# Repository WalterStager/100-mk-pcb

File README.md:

# 100-mk-pcb
PCB design for 100% mechanical keyboard

Libraries used in this project  
https://github.com/tmk/kicad_lib_tmk  
https://github.com/tmk/keyboard_parts.pretty  
https://github.com/egladman/keebs.pretty  
https://github.com/ai03-2725/Type-C.pretty

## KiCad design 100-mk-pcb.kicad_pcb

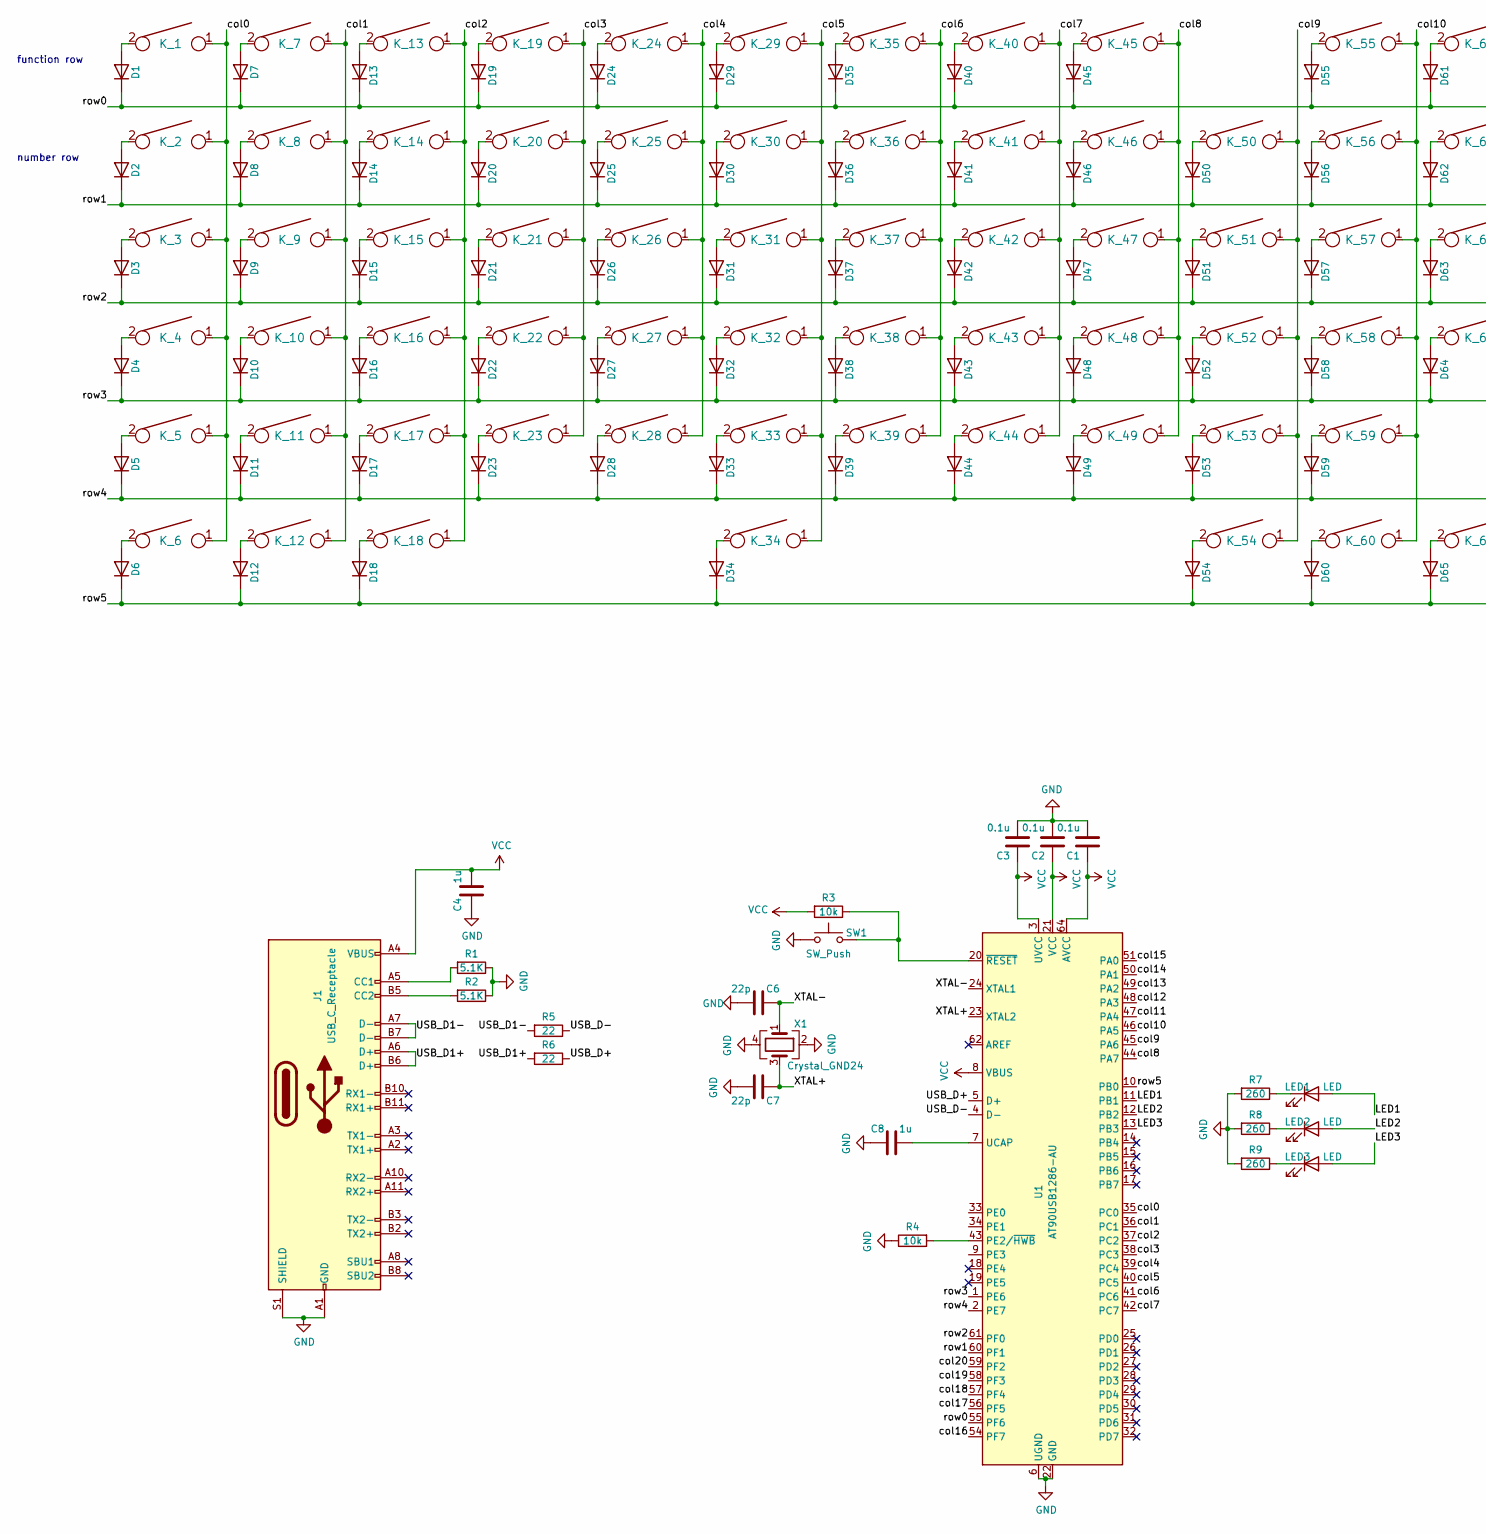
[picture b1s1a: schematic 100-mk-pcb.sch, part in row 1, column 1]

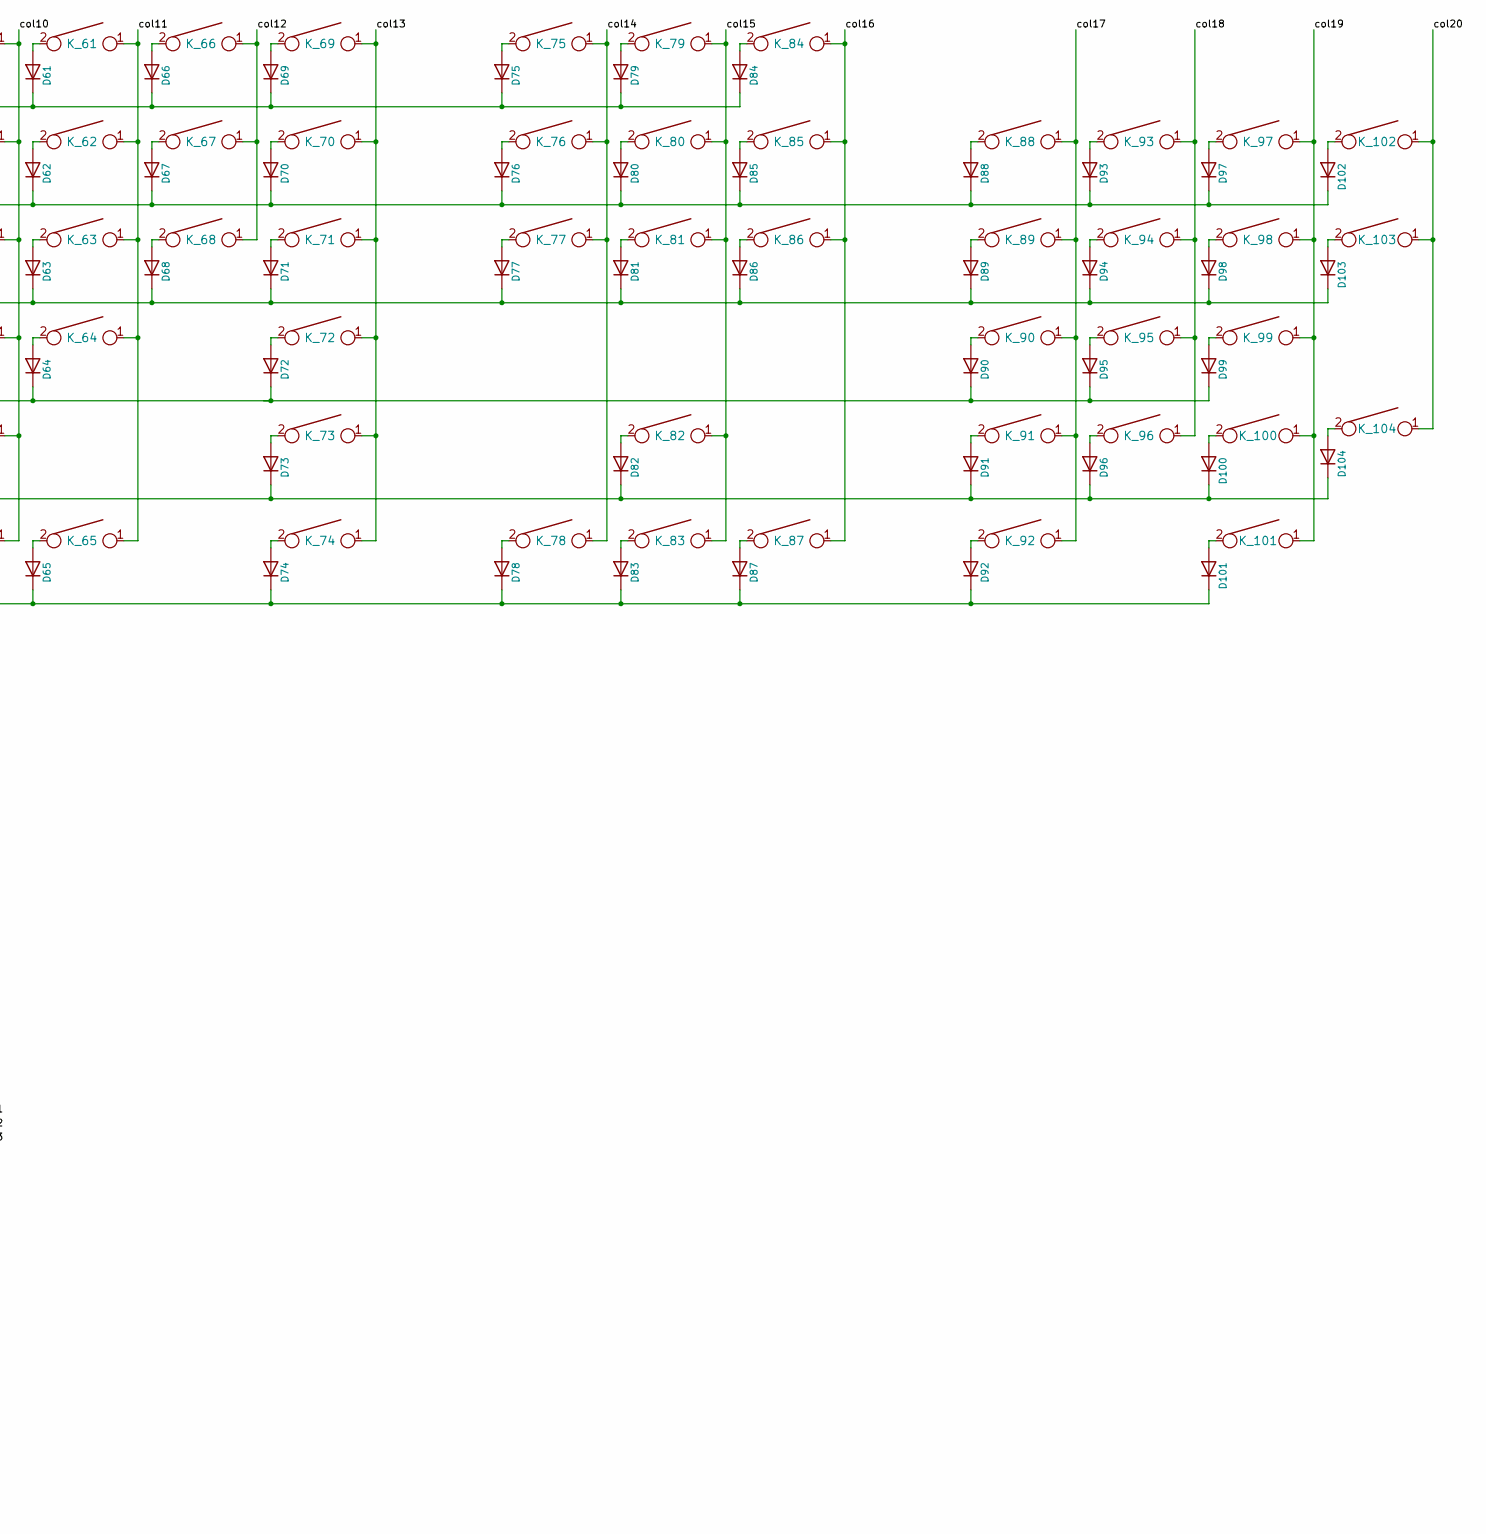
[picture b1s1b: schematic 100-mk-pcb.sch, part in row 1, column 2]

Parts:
C1, C2, C3: 0.1u; C_0805_2012Metric_Pad1.18x1.45mm_HandSolder
C4, C8: 1u; C_0805_2012Metric_Pad1.18x1.45mm_HandSolder
C6, C7: 22p; C_0805_2012Metric_Pad1.18x1.45mm_HandSolder
D1, D2, D3, D4, D5, D6, D7, D8, D9, D10, D11, D12, D13, D14, D15, D16, D17, D18, D19, D20, D21, D22, D23, D24, D25, D26, D27, D28, D29, D30, D31, D32, D33, D34, D35, D36, D37, D38, D39, D40, D41, D42, D43, D44, D45, D46, D47, D48, D49, D50, D51, D52, D53, D54, D55, D56, D57, D58, D59, D60, D61, D62, D63, D64, D65, D66, D67, D68, D69, D70, D71, D72, D73, D74, D75, D76, D77, D78, D79, D80, D81, D82, D83, D84, D85, D86, D87, D88, D89, D90, D91, D92, D93, D94, D95, D96, D97, D98, D99, D100, D101, D102, D103, D104: D; D_SOD123_axial
J1: USB_C_Receptacle; USB_C_GCT_USB4085
K_1, K_2, K_7, K_8, K_9, K_10, K_11, K_12, K_13, K_14, K_15, K_16, K_17, K_19, K_20, K_21, K_22, K_23, K_24, K_25, K_26, K_27, K_28, K_29, K_30, K_31, K_32, K_33, K_35, K_36, K_37, K_38, K_39, K_40, K_41, K_42, K_43, K_44, K_45, K_46, K_47, K_48, K_49, K_50, K_51, K_52, K_53, K_55, K_56, K_57, K_58, K_59, K_60, K_61, K_62, K_63, K_64, K_65, K_66, K_67, K_68, K_69, K_75, K_76, K_77, K_78, K_79, K_80, K_81, K_82, K_83, K_84, K_85, K_86, K_87, K_88, K_89, K_90, K_91, K_93, K_94, K_95, K_96, K_97, K_98, K_99, K_100, K_101, K_102: KEYSW; SW_Cherry_MX_1.00u_PCB
K_3, K_6, K_54, K_71, K_74: KEYSW; SW_Cherry_MX_1.50u_PCB
K_4: KEYSW; SW_Cherry_MX_1.75u_PCB
K_5, K_72: KEYSW; SW_Cherry_MX_2.25u_PCB
K_18: KEYSW; SW_Cherry_MX_1.25u_PCB
K_34: KEYSW; SW_Cherry_MX_6.25u_PCB
K_70, K_92: KEYSW; SW_Cherry_MX_2.00u_PCB
K_73: KEYSW; SW_Cherry_MX_2.75u_PCB
K_103, K_104: KEYSW; SW_Cherry_MX_2.00u_Vertical_PCB
LED1, LED2, LED3: LED; LED_0805_2012Metric_Pad1.15x1.40mm_HandSolder
R1, R2: 5.1K; R_0805_2012Metric_Pad1.20x1.40mm_HandSolder
R3, R4: 10k; R_0805_2012Metric_Pad1.20x1.40mm_HandSolder
R5, R6: 22; R_0805_2012Metric_Pad1.20x1.40mm_HandSolder
R7, R8, R9: 260; R_0805_2012Metric_Pad1.20x1.40mm_HandSolder
SW1: SW_Push; SW_SPST_TL3342
U1: AT90USB1286-AU
X1: Crystal_GND24; Crystal_SMD_SeikoEpson_TSX3225-4Pin_3.2x2.5mm_HandSoldering

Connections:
/LED1: LED1.2 (A), U1.11 (PB1); also elsewhere on the board
/LED2: LED2.2 (A), U1.12 (PB2); also elsewhere on the board
/LED3: LED3.2 (A), U1.13 (PB3); also elsewhere on the board
/USB_D1+: J1.A6 (D+), J1.B6 (D+), R6.2
/USB_D1-: J1.A7 (D-), J1.B7 (D-), R5.2
/USB_D+: R6.1, U1.5 (D+)
/USB_D-: R5.1, U1.4 (D-)
/XTAL+: C7.1, U1.23 (XTAL2), X1.3
/XTAL-: C6.1, U1.24 (XTAL1), X1.1
/col0: K_1.1, K_2.1, K_3.1, K_4.1, K_5.1, K_6.1, U1.35 (PC0)
/col1: K_7.1, K_8.1, K_9.1, K_10.1, K_11.1, K_12.1, U1.36 (PC1)
/col2: K_13.1, K_14.1, K_15.1, K_16.1, K_17.1, K_18.1, U1.37 (PC2)
/col3: K_19.1, K_20.1, K_21.1, K_22.1, K_23.1, U1.38 (PC3)
/col4: K_24.1, K_25.1, K_26.1, K_27.1, K_28.1, U1.39 (PC4)
/col5: K_29.1, K_30.1, K_31.1, K_32.1, K_33.1, K_34.1, U1.40 (PC5)
/col6: K_35.1, K_36.1, K_37.1, K_38.1, K_39.1, U1.41 (PC6)
/col7: K_40.1, K_41.1, K_42.1, K_43.1, K_44.1, U1.42 (PC7)
/col8: K_45.1, K_46.1, K_47.1, K_48.1, K_49.1, U1.44 (PA7)
/col9: K_50.1, K_51.1, K_52.1, K_53.1, K_54.1, U1.45 (PA6)
/col10: K_55.1, K_56.1, K_57.1, K_58.1, K_59.1, K_60.1, U1.46 (PA5)
/col11: K_61.1, K_62.1, K_63.1, K_64.1, K_65.1, U1.47 (PA4)
/col12: K_66.1, K_67.1, K_68.1, U1.48 (PA3)
/col13: K_69.1, K_70.1, K_71.1, K_72.1, K_73.1, K_74.1, U1.49 (PA2)
/col14: K_75.1, K_76.1, K_77.1, K_78.1, U1.50 (PA1)
/col15: K_79.1, K_80.1, K_81.1, K_82.1, K_83.1, U1.51 (PA0)
/col16: K_84.1, K_85.1, K_86.1, K_87.1, U1.54 (PF7)
/col17: K_88.1, K_89.1, K_90.1, K_91.1, K_92.1, U1.56 (PF5)
/col18: K_93.1, K_94.1, K_95.1, K_96.1, U1.57 (PF4)
/col19: K_97.1, K_98.1, K_99.1, K_100.1, K_101.1, U1.58 (PF3)
/col20: K_102.1, K_103.1, K_104.1, U1.59 (PF2)
/row0: D1.1 (K), D7.1 (K), D13.1 (K), D19.1 (K), D24.1 (K), D29.1 (K), D35.1 (K), D40.1 (K), D45.1 (K), D55.1 (K), D61.1 (K), D66.1 (K), D69.1 (K), D75.1 (K), D79.1 (K), D84.1 (K), U1.55 (PF6)
/row1: D2.1 (K), D8.1 (K), D14.1 (K), D20.1 (K), D25.1 (K), D30.1 (K), D36.1 (K), D41.1 (K), D46.1 (K), D50.1 (K), D56.1 (K), D62.1 (K), D67.1 (K), D70.1 (K), D76.1 (K), D80.1 (K), D85.1 (K), D88.1 (K), D93.1 (K), D97.1 (K), D102.1 (K), U1.60 (PF1)
/row2: D3.1 (K), D9.1 (K), D15.1 (K), D21.1 (K), D26.1 (K), D31.1 (K), D37.1 (K), D42.1 (K), D47.1 (K), D51.1 (K), D57.1 (K), D63.1 (K), D68.1 (K), D71.1 (K), D77.1 (K), D81.1 (K), D86.1 (K), D89.1 (K), D94.1 (K), D98.1 (K), D103.1 (K), U1.61 (PF0)
/row3: D4.1 (K), D10.1 (K), D16.1 (K), D22.1 (K), D27.1 (K), D32.1 (K), D38.1 (K), D43.1 (K), D48.1 (K), D52.1 (K), D58.1 (K), D64.1 (K), D72.1 (K), D90.1 (K), D95.1 (K), D99.1 (K), U1.1 (PE6)
/row4: D5.1 (K), D11.1 (K), D17.1 (K), D23.1 (K), D28.1 (K), D33.1 (K), D39.1 (K), D44.1 (K), D49.1 (K), D53.1 (K), D59.1 (K), D73.1 (K), D82.1 (K), D91.1 (K), D96.1 (K), D100.1 (K), D104.1 (K), U1.2 (PE7)
/row5: D6.1 (K), D12.1 (K), D18.1 (K), D34.1 (K), D54.1 (K), D60.1 (K), D65.1 (K), D74.1 (K), D78.1 (K), D83.1 (K), D87.1 (K), D92.1 (K), D101.1 (K), U1.10 (PB0)
GND: C1.2, C2.2, C3.2, C4.2, C6.2, C7.2, C8.2, J1.A1 (GND), J1.A12 (GND), J1.B1 (GND), J1.B12 (GND), J1.S1 (SHIELD), R1.1, R2.1, R4.1, R7.2, R8.2, R9.2, SW1.1, U1.6 (UGND), U1.22 (GND), U1.53 (GND), U1.63 (GND), X1.2, X1.4
unnamed: C8.1, U1.7 (UCAP)
unnamed: D1.2 (A), K_1.2
unnamed: D2.2 (A), K_2.2
unnamed: D3.2 (A), K_3.2
unnamed: D4.2 (A), K_4.2
unnamed: D5.2 (A), K_5.2
unnamed: D6.2 (A), K_6.2
unnamed: D7.2 (A), K_7.2
unnamed: D8.2 (A), K_8.2
unnamed: D9.2 (A), K_9.2
unnamed: D10.2 (A), K_10.2
unnamed: D11.2 (A), K_11.2
unnamed: D12.2 (A), K_12.2
unnamed: D13.2 (A), K_13.2
unnamed: D14.2 (A), K_14.2
unnamed: D15.2 (A), K_15.2
unnamed: D16.2 (A), K_16.2
unnamed: D17.2 (A), K_17.2
unnamed: D18.2 (A), K_18.2
unnamed: D19.2 (A), K_19.2
unnamed: D20.2 (A), K_20.2
unnamed: D21.2 (A), K_21.2
unnamed: D22.2 (A), K_22.2
unnamed: D23.2 (A), K_23.2
unnamed: D24.2 (A), K_24.2
unnamed: D25.2 (A), K_25.2
unnamed: D26.2 (A), K_26.2
unnamed: D27.2 (A), K_27.2
unnamed: D28.2 (A), K_28.2
unnamed: D29.2 (A), K_29.2
unnamed: D30.2 (A), K_30.2
unnamed: D31.2 (A), K_31.2
unnamed: D32.2 (A), K_32.2
unnamed: D33.2 (A), K_33.2
unnamed: D34.2 (A), K_34.2
unnamed: D35.2 (A), K_35.2
unnamed: D36.2 (A), K_36.2
unnamed: D37.2 (A), K_37.2
unnamed: D38.2 (A), K_38.2
unnamed: D39.2 (A), K_39.2
unnamed: D40.2 (A), K_40.2
unnamed: D41.2 (A), K_41.2
unnamed: D42.2 (A), K_42.2
unnamed: D43.2 (A), K_43.2
unnamed: D44.2 (A), K_44.2
unnamed: D45.2 (A), K_45.2
unnamed: D46.2 (A), K_46.2
unnamed: D47.2 (A), K_47.2
unnamed: D48.2 (A), K_48.2
unnamed: D49.2 (A), K_49.2
unnamed: D50.2 (A), K_50.2
unnamed: D51.2 (A), K_51.2
unnamed: D52.2 (A), K_52.2
unnamed: D53.2 (A), K_53.2
unnamed: D54.2 (A), K_54.2
unnamed: D55.2 (A), K_55.2
unnamed: D56.2 (A), K_56.2
unnamed: D57.2 (A), K_57.2
unnamed: D58.2 (A), K_58.2
unnamed: D59.2 (A), K_59.2
unnamed: D60.2 (A), K_60.2
unnamed: D61.2 (A), K_61.2
unnamed: D62.2 (A), K_62.2
unnamed: D63.2 (A), K_63.2
unnamed: D64.2 (A), K_64.2
unnamed: D65.2 (A), K_65.2
unnamed: D66.2 (A), K_66.2
unnamed: D67.2 (A), K_67.2
unnamed: D68.2 (A), K_68.2
unnamed: D69.2 (A), K_69.2
unnamed: D70.2 (A), K_70.2
unnamed: D71.2 (A), K_71.2
unnamed: D72.2 (A), K_72.2
unnamed: D73.2 (A), K_73.2
unnamed: D74.2 (A), K_74.2
unnamed: D75.2 (A), K_75.2
unnamed: D76.2 (A), K_76.2
unnamed: D77.2 (A), K_77.2
unnamed: D78.2 (A), K_78.2
unnamed: D79.2 (A), K_79.2
unnamed: D80.2 (A), K_80.2
unnamed: D81.2 (A), K_81.2
unnamed: D82.2 (A), K_82.2
unnamed: D83.2 (A), K_83.2
unnamed: D84.2 (A), K_84.2
unnamed: D85.2 (A), K_85.2
unnamed: D86.2 (A), K_86.2
unnamed: D87.2 (A), K_87.2
unnamed: D88.2 (A), K_88.2
unnamed: D89.2 (A), K_89.2
unnamed: D90.2 (A), K_90.2
unnamed: D91.2 (A), K_91.2
unnamed: D92.2 (A), K_92.2
unnamed: D93.2 (A), K_93.2
unnamed: D94.2 (A), K_94.2
unnamed: D95.2 (A), K_95.2
unnamed: D96.2 (A), K_96.2
unnamed: D97.2 (A), K_97.2
unnamed: D98.2 (A), K_98.2
unnamed: D99.2 (A), K_99.2
unnamed: D100.2 (A), K_100.2
unnamed: D101.2 (A), K_101.2
unnamed: D102.2 (A), K_102.2
unnamed: D103.2 (A), K_103.2
unnamed: D104.2 (A), K_104.2
unnamed: J1.A5 (CC1), R1.2
unnamed: J1.B5 (CC2), R2.2
unnamed 146: LED1.1 (K), R7.1; also elsewhere on the board
unnamed 147: LED2.1 (K), R8.1; also elsewhere on the board
unnamed 148: LED3.1 (K), R9.1; also elsewhere on the board
unnamed: R3.1, SW1.2, U1.20 (~RESET)
unnamed: R4.2, U1.43 (PE2/~HWB)
VCC: C1.1, C2.1, C3.1, C4.1, J1.A4 (VBUS), J1.A9 (VBUS), J1.B4 (VBUS), J1.B9 (VBUS), R3.2, U1.3 (UVCC), U1.8 (VBUS), U1.21 (VCC), U1.52 (VCC), U1.64 (AVCC)

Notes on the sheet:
function row
number row

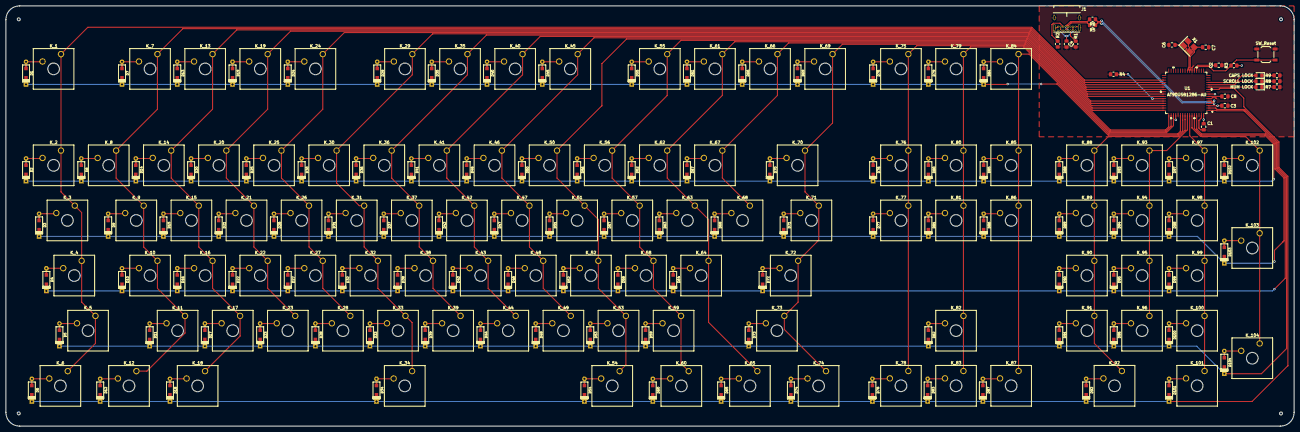
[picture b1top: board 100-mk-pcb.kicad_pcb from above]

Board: 2 copper layers, 442.9 x 144.5 mm, 231 parts (0 on the bottom side), 150 nets.

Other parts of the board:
CAPS LOCK: LED; LED_0805_2012Metric_Pad1.15x1.40mm_HandSolder
NUM LOCK: LED; LED_0805_2012Metric_Pad1.15x1.40mm_HandSolder
SCROLL LOCK: LED; LED_0805_2012Metric_Pad1.15x1.40mm_HandSolder

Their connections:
/LED1: NUM LOCK.2; also elsewhere on the board
/LED2: SCROLL LOCK.2; also elsewhere on the board
/LED3: CAPS LOCK.2; also elsewhere on the board
unnamed 146: NUM LOCK.1; also elsewhere on the board
unnamed 147: SCROLL LOCK.1; also elsewhere on the board
unnamed 148: CAPS LOCK.1; also elsewhere on the board

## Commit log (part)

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2021-04-18 updated schematic and pcb
2025-06-28 Rename project

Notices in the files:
parts and their libraries:
Copyright 2016 Accelerated Designs. All rights reserved.
